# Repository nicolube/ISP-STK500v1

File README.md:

# ISP an Hand einer STK500v1
Diese ISP ist im grunde einer [STK500v1](http://ww1.microchip.com/downloads/en/Appnotes/doc2525.pdf) auch bekannt als [Arduino as ISP](https://www.arduino.cc/en/Tutorial/BuiltInExamples/ArduinoISP) mit der erweitern Schnittstelle für das [ATMega32 Board](/ATMega32%20Board/ATMega32%20Board.pdf) der IHK.
## Inhaltsverzeichnis
- [ISP an Hand einer STK500v1](#isp-an-hand-einer-stk500v1)
  - [Inhaltsverzeichnis](#inhaltsverzeichnis)
- [Bedienung](#bedienung)
  - [Jumper](#jumper)
  - [Arduino IDE](#arduino-ide)
  - [PlatformIO](#platformio)
  - [Schnittstellen Beschreibung](#schnittstellen-beschreibung)
- [Bauteile die vernachlässicht werden können](#bauteile-die-vernachlässicht-werden-können)
- [Programmieren der ISP](#programmieren-der-isp)
  - [Flashen der Firmware](#flashen-der-firmware)
- [Bestückungsplan](#bestückungsplan)
- [Schaltplan](#schaltplan)

# Bedienung

Das Board ist wie am Anfang genant eine STK500v1 und verhält sich auch so. Es registriert sich auf der Seite des PC als Serielle Schnittstelle.

Bevor Sie jedoch ihr zu Programirendes Board anschießen muss geprüft werden ob das zu programmirende Board eine eigene Spannungsversorgung hat und ob diese auf die AVR ISP Schnittstelle geführt wird. Sollte dies der Fall sein so entfernen Sie bitte JP2.

## Jumper

- ### JP1 Programmier Modus 
  
  JP1 muss im normalfall immer auf der Stellung (2,3) sein.
In der Stellung (1,2) ist die ISP im Selbst Programmiermodus und kann durch eine andere ISP geflasht werden. 

- ### JP2 Spannung über ISP

  Wenn die zu programmirende Board eine Stromaufnahme unter 100mA besitzt kann JP2 dazu genutzt werden die Board mit Spannung zu versorgen. **Dies darf nur im Spannungfreien zustand des Bords genutzt werden**

## Arduino IDE

Wählen Sie unter Tools den Port Ihrer STK500v1 und den Programmer *Arduino as ISP*.
Jetzt kann wie gewohnt ihr Programm hochgeladen werden.

Für genauere Informationen Klicken Sie [hier](https://www.arduino.cc/en/Tutorial/BuiltInExamples/ArduinoISP#program-the-bootloader) 

## PlatformIO

Bitte nutzen Sie für PlatformIO Projekt unser [Beispiel Projekt](/ISP/Beispiel).
Hier bei ist zu Beachten das in der [platform.ini](/ISP/Beispiel/platformio.ini) der *upload_port* angepasst werden muss.

## Schnittstellen Beschreibung

- SV1 und SV2 sind eine 6-, 10-Pin [AVR ISP Schittstelle](https://telecnatron.com/reference/pinouts/avr-isp/index.html).
- X1 ist ebenfalls eine ISP jedoch adoptiert auf den Parallelen Port des [ATMega32 Board](/ATMega32%20Board/ATMega32%20Board.pdf)
- X2 [USB Type B](https://static.giga.de/wp-content/uploads/2015/06/USB-2.0-A-B-Pins.png) zur Kommunikation mit dem PC.

# Bauteile die vernachlässicht werden können
Die Leiterplatte hat verschiedene Zusatzkomponenten die für die Funktion nicht zwingen benötigt werden, jedoch zusätzliche sicherheiten gewähren.

- Entstörkondensatoren USB (C8, C9)
- ESD-Schutz Diodennetzwerk (U1)
- FT232: Reset Pulldown (R5)
- FT232: 3,3V Entstörer (C7)

# Programmieren der ISP

Zum Programiren der ISP muss JP1 (1,2) und JP2 gesetzt werden.
Nun kann mittels einer anderen ISP die [Firmware](/ISP/Firmware/) geflasht werden.
Zudem muss SV1 oder SV2 auf ein Programmiergerät gebückt werden, dies kann z.b. eine USBASP oder eine andere ISP sein.

**Prüfen Sie die Stellung der Jumper!**

## Flashen der Firmware
1. Begeben Sie sich in den Verzeichnis des Projektes.
2. Prüfen Sie in der [platform.ini](/ISP/Firmware/platformio.ini) ob Sie den richtigen *upload_port* gewählt haben.
3. Öffenen Sie nun ein Terminal / CMD die [PlatformIO CLI](https://platformio.org/install/cli) installiert hat.
4. Setzen Sie die Fuses des Mikrocontrollers mit ```pio run --target fuses```.
5. Laden Sie nun die Firmware mit ```pio run --target upload``` hoch.

>  Bitte beachten Sie das der Jumper JP1 zur normalen nutzung wieder auf JP1 (2,3) gesetzt werden muss.

# Bestückungsplan
**Siehe [Stückliste](/ISP/Eagle/Stückliste.txt) für Bauteilinformation.**

# Schaltplan

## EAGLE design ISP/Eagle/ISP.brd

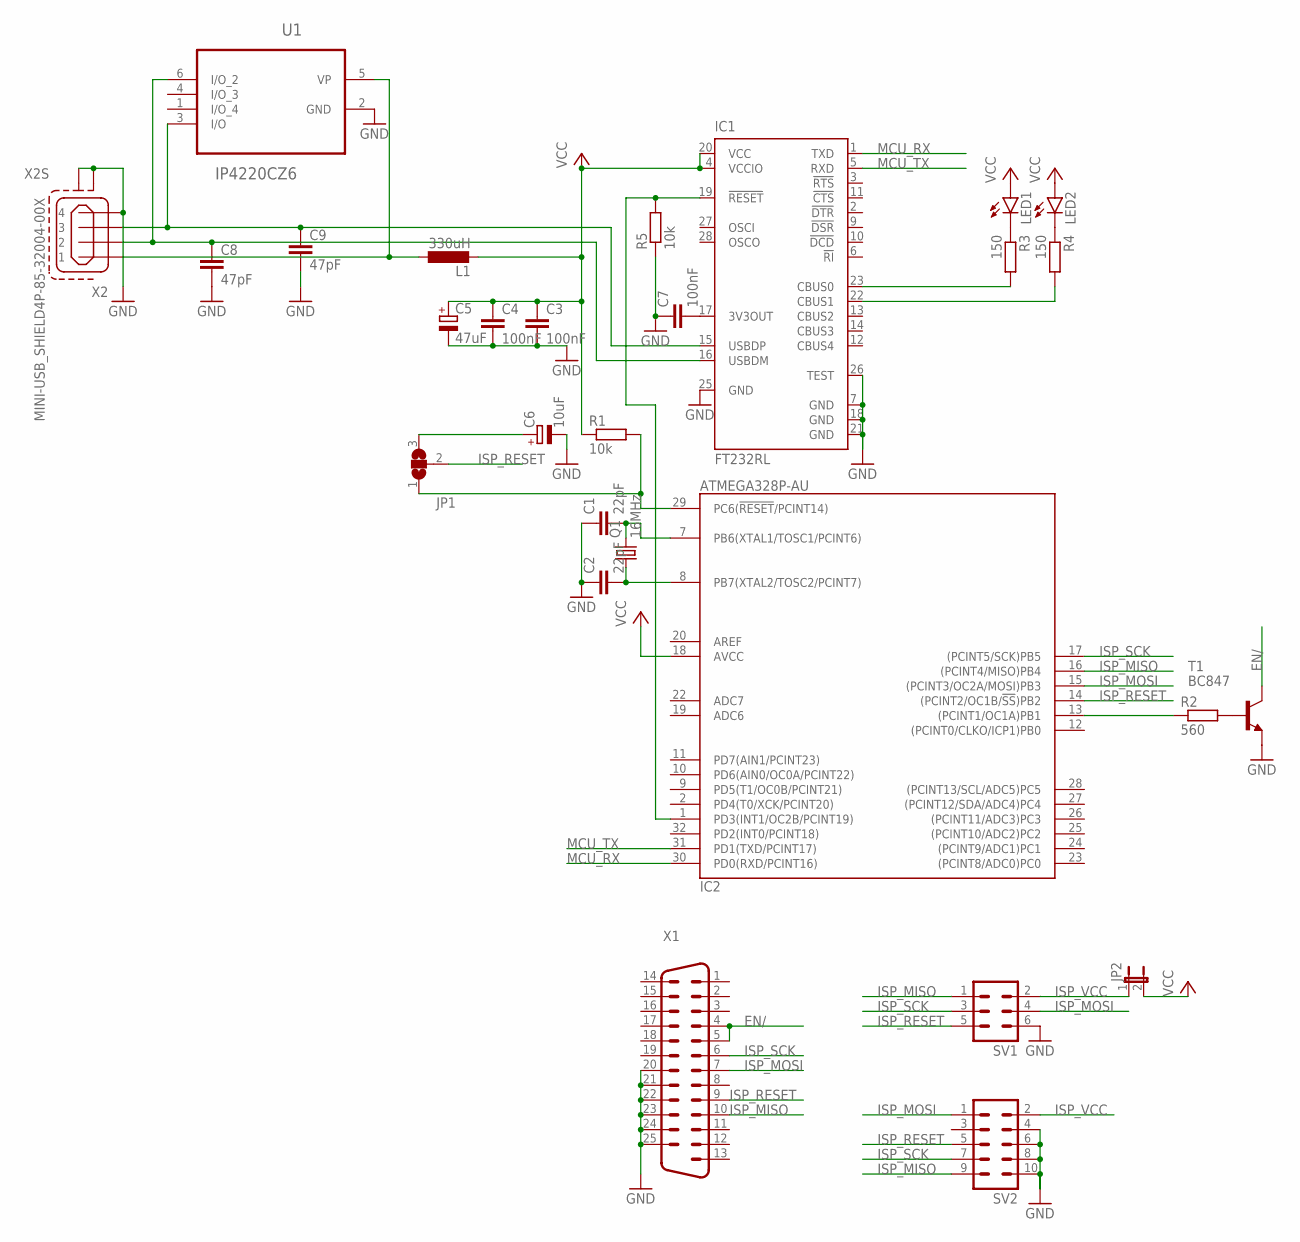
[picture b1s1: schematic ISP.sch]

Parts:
C1, C2: 22pF; C0805
C3, C4, C7: 100nF; C0805
C5: 47uF; PANASONIC_D
C6: 10uF; PANASONIC_C
C8, C9: 47pF; C0805
IC1: FT232RL; SSOP28
IC2: ATMEGA328P-AU; QFP32_7X7_0.80
JP1: SJ2W; SJ_2
JP2: JP1E; JP1
L1: 330uH; L1812
LED1, LED2: LEDCHIPLED_1206; CHIPLED_1206
Q1: 16MHz; HC49UP
R1, R5: 10k; R0805
R2: 560; R0805
R3, R4: 150; R0805
SV1: ML6
SV2: ML10
T1: BC847; SOT23
U1: IP4220CZ6; SOT95P275X110-6N
X1: M25HP
X2: MINI-USB_SHIELD4P-85-32004-00X; 85-32004-00X

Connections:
EN/: T1.3 (C), X1.4, X1.5
GND: C1.1, C2.1, C3.2, C4.2, C5.-, C6.-, C7.1, C8.2, C9.2, IC1.7 (GND), IC1.18 (GND), IC1.21 (GND), IC1.25 (GND), IC1.26 (TEST), IC2.3 (GND), IC2.5 (GND), IC2.21 (GND), R5.1, SV1.6, SV2.4, SV2.6, SV2.8, SV2.10, T1.2 (E), U1.2 (GND), X1.20, X1.21, X1.22, X1.23, X1.24, X1.25, X2.4, X2.M1 (S1), X2.M2 (S2)
ISP_MISO: IC2.16 ((PCINT4/MISO)PB4), SV1.1, SV2.9, X1.10
ISP_MOSI: IC2.15 ((PCINT3/OC2A/MOSI)PB3), SV1.4, SV2.1, X1.7
ISP_RESET: IC2.14 ((PCINT2/OC1B/!SS!)PB2), JP1.2, SV1.5, SV2.5, X1.9
ISP_SCK: IC2.17 ((PCINT5/SCK)PB5), SV1.3, SV2.7, X1.6
ISP_VCC: JP2.1, SV1.2, SV2.2
MCU_RX: IC1.1 (TXD), IC2.30 (PD0(RXD/PCINT16))
MCU_TX: IC1.5 (RXD), IC2.31 (PD1(TXD/PCINT17))
unnamed: IC2.29 (PC6(!RESET!/PCINT14)), JP1.1, R1.2
unnamed: C6.+, JP1.3
unnamed: C1.2, IC2.7 (PB6(XTAL1/TOSC1/PCINT6)), Q1.2
unnamed: C9.1, IC1.15 (USBDP), U1.3 (I/O), X2.3
unnamed: IC2.13 ((PCINT1/OC1A)PB1), R2.1
unnamed: R2.2, T1.1 (B)
unnamed: C8.1, IC1.16 (USBDM), U1.6 (I/O_2), X2.2
unnamed: C7.2, IC1.17 (3V3OUT)
unnamed: C2.2, IC2.8 (PB7(XTAL2/TOSC2/PCINT7)), Q1.1
unnamed: LED2.C, R4.1
unnamed: LED1.C, R3.1
unnamed: IC1.23 (CBUS0), R3.2
unnamed: IC1.22 (CBUS1), R4.2
unnamed: L1.1, U1.5 (VP), X2.1
unnamed: IC1.19 (!RESET), IC2.1 (PD3(INT1/OC2B/PCINT19)), R5.2
VCC: C3.1, C4.1, C5.+, IC1.4 (VCCIO), IC1.20 (VCC), IC2.4 (VCC), IC2.6 (VCC), IC2.18 (AVCC), JP2.2, L1.2, LED1.A, LED2.A, R1.1

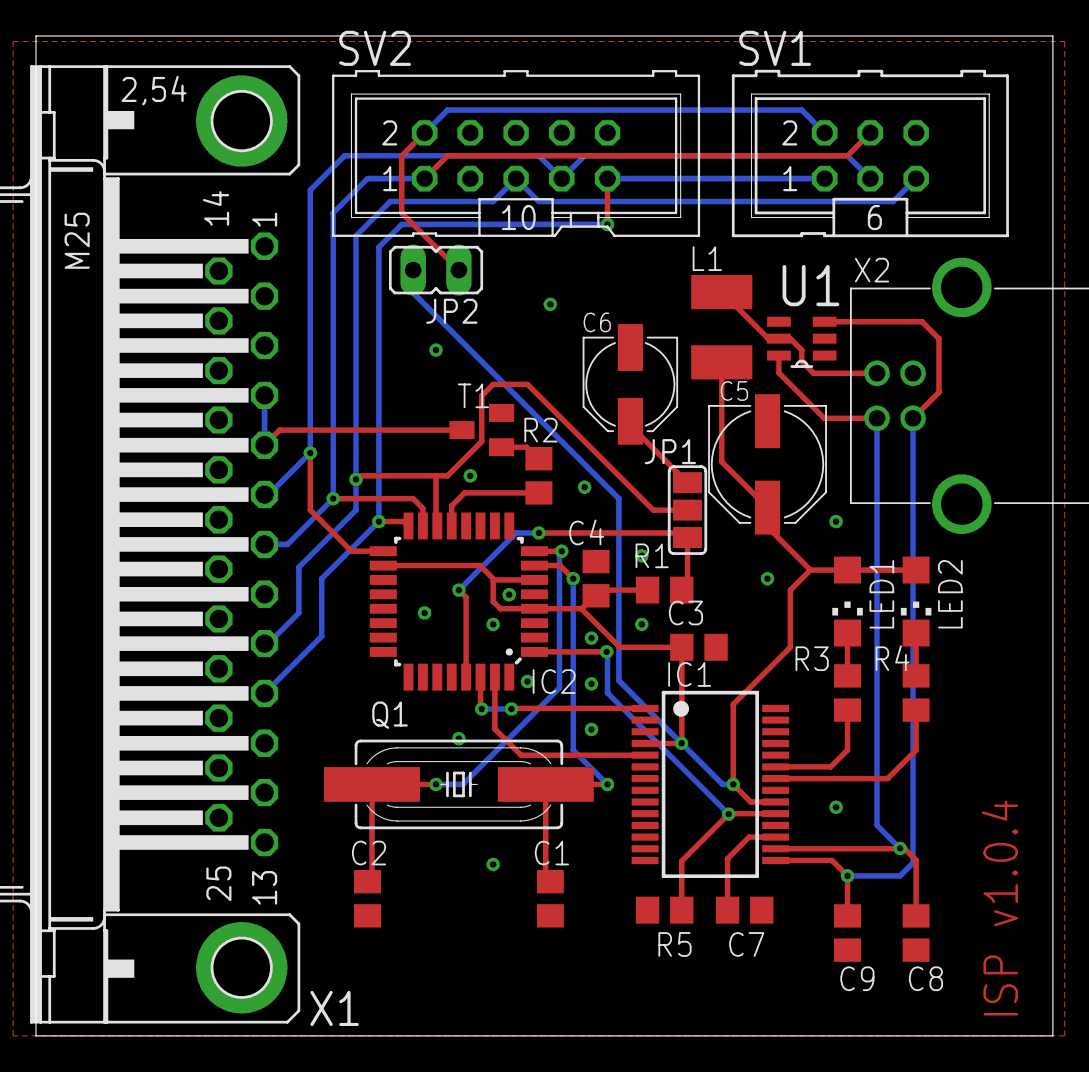
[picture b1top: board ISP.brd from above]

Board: 2 copper layers, 56.5 x 55.5 mm, 28 parts (0 on the bottom side), 25 nets.

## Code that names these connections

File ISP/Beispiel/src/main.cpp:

#include <Arduino.h>
#include <LiquidCrystal.h>

LiquidCrystal lcd(PB0, PB1, PB2, PB4, PB5, PB6, PB7);



void setup() {
  Serial.begin(9600);
  Serial.println("Init");
  lcd.begin(16,2);
  lcd.backlight();
  lcd.home();
  lcd.print("AP Winter 2021");
  lcd.setCursor(0,1);
  lcd.print("Demo");
  delay(2000);
  lcd.clear();
}

void loop() {

  lcd.home();
  lcd.print("PA0: ");
  lcd.print(analogRead(PA0)*0.004882813);
  lcd.print("V   ");
  lcd.setCursor(0,1);
  lcd.print("PA1: ");
  lcd.print(analogRead(PA1)*0.004882813);
  lcd.print("V   ");

}

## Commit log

2021-03-26 Init
2021-03-26 Add Firmare and Example code
2021-03-26 Fix woring word
2021-03-26 Fix spelling mistakes
2021-03-26 Fixing Spelling mistakes
2021-03-26 Fixing docu mistake
2021-03-26 Fix naming mistake
2021-03-26 Added Juper description
2021-03-30 fixes
2021-04-01 Shorten the Curcit Board
